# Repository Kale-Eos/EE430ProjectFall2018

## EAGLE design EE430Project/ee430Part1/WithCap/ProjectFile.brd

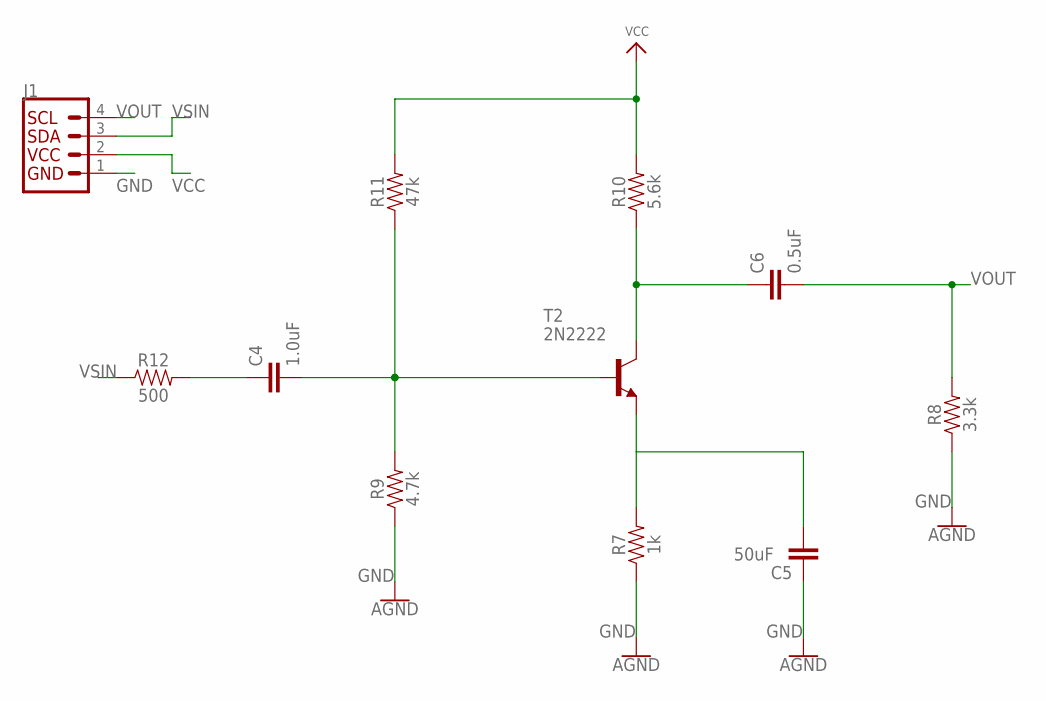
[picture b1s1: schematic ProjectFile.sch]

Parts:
C4: 1.0uF; 0603
C5: 50uF; 0603
C6: 0.5uF; 0603
J1: QWIIC_CONNECTORJS-1MM; 1X04_1MM_RA
R7: 1k; 0603
R8: 3.3k; 0603
R9: 4.7k; 0603
R10: 5.6k; 0603
R11: 47k; 0603
R12: 500; 0603
T2: 2N2222; TO92-EBC-OVAL

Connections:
GND: C5.1, J1.1 (GND), R7.1, R8.1, R9.1
unnamed: C6.1, R10.1, T2.C
unnamed: C5.2, R7.2, T2.E
unnamed: C4.2, R9.2, R11.1, T2.B
unnamed: C4.1, R12.2
VCC: J1.2 (VCC), R10.2, R11.2
VOUT: C6.2, J1.4 (SCL), R8.2
VSIN: J1.3 (SDA), R12.1

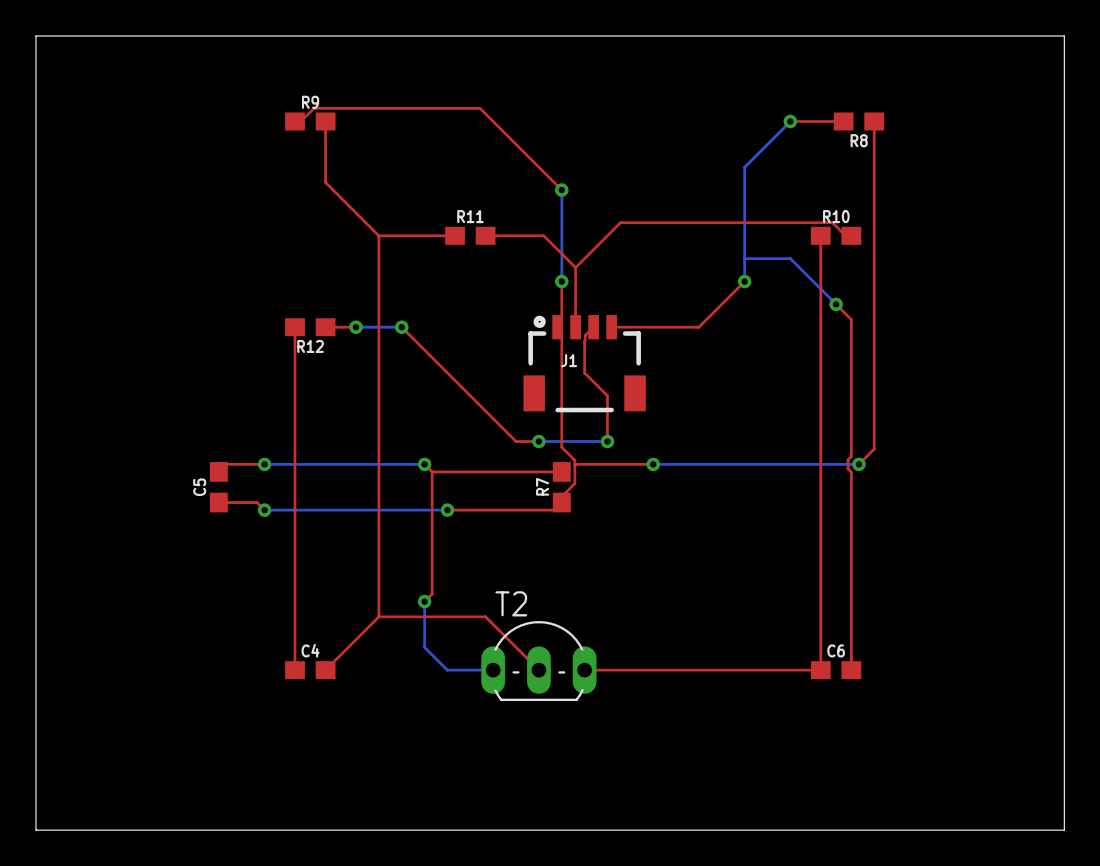
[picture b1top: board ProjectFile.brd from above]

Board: 2 copper layers, 57.1 x 44.1 mm, 11 parts (0 on the bottom side), 8 nets.

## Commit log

2018-11-30 included project instructions and lab 5(4) circuit diagram
2018-12-03 Eagle file start
2018-12-06 Hi Paco
2018-12-07 Just added the output label, i think we are ready to do rats nest next
2018-12-13 All the Eagle file necessary for the project Part 1 == has bypass capacitor Part 2 == has no bypass capacitor
2018-12-13 added in the powerpoint

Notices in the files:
parts and their libraries:
SparkFun-Capacitors: Licensing: Creative Commons ShareAlike 4.0 International - https://creativecommons.org/licenses/by-sa/4.0
